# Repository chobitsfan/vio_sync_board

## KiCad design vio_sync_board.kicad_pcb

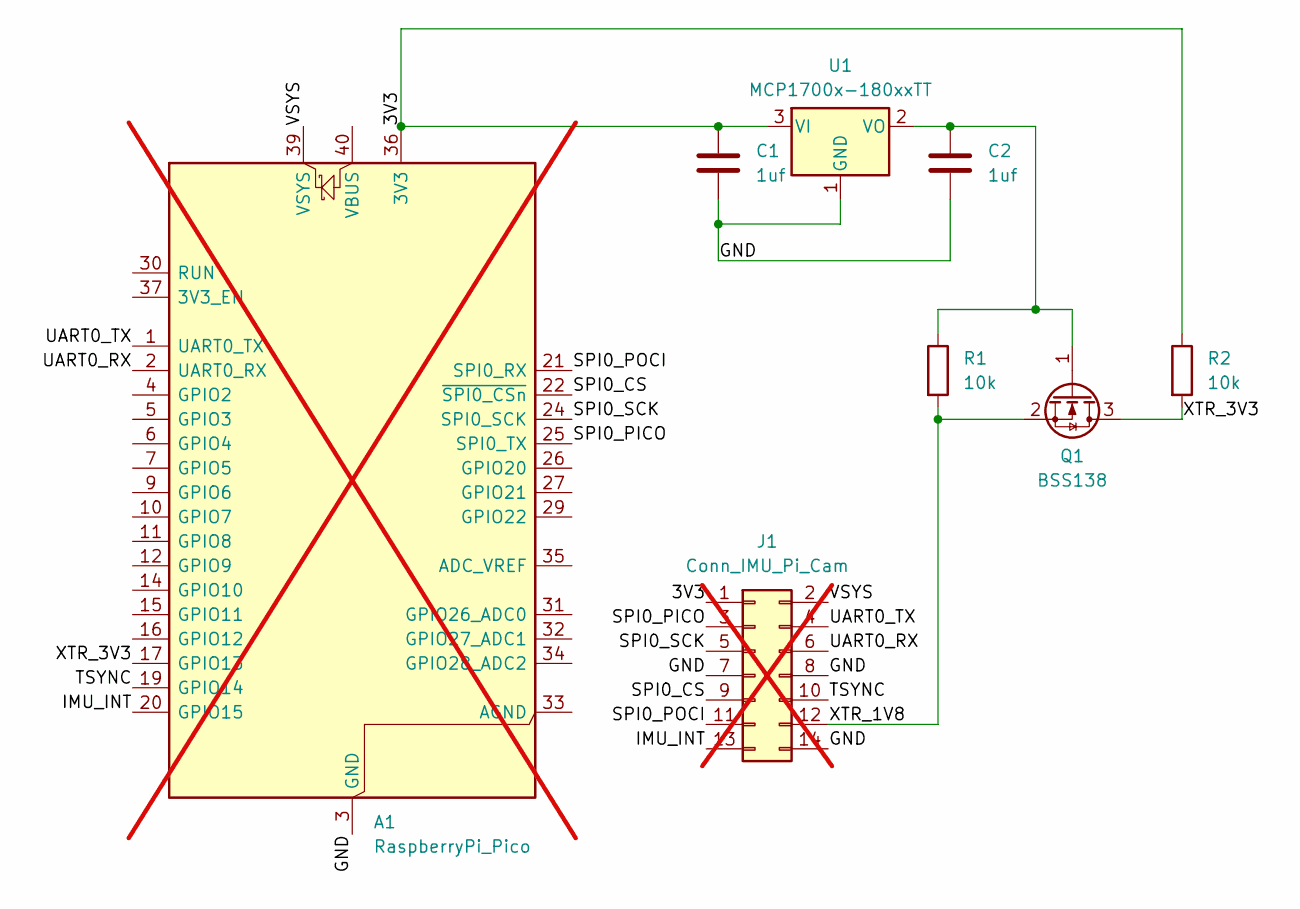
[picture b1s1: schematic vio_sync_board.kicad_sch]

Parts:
A1: RaspberryPi_Pico; RaspberryPi_Pico_Common_THT; not fitted
C1, C2: 1uf; C_0805_2012Metric
J1: Conn_IMU_Pi_Cam; PinHeader_2x07_P2.54mm_Vertical; not fitted
Q1: BSS138; SOT-23
R1, R2: 10k; R_0805_2012Metric
U1: MCP1700x-180xxTT; SOT-23

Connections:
/3V3: A1.36 (3V3), C1.1, J1.1, R2.1, U1.3 (VI)
/GND: A1.3 (GND), A1.8 (GND), A1.13 (GND), A1.18 (GND), A1.23 (GND), A1.28 (GND), A1.38 (GND), C1.2, C2.2, J1.7, J1.8, J1.14, U1.1 (GND)
/IMU_INT: A1.20 (GPIO15), J1.13
/SPI0_CS: A1.22 (~SPI0_CSn), J1.9
/SPI0_PICO: A1.25 (SPI0_TX), J1.3
/SPI0_POCI: A1.21 (SPI0_RX), J1.11
/SPI0_SCK: A1.24 (SPI0_SCK), J1.5
/TSYNC: A1.19 (GPIO14), J1.10
/UART0_RX: A1.2 (UART0_RX), J1.6
/UART0_TX: A1.1 (UART0_TX), J1.4
/VSYS: A1.39 (VSYS), J1.2
/XTR_1V8: J1.12, Q1.2 (S), R1.2
/XTR_3V3: A1.17 (GPIO13), Q1.3 (D), R2.2
unnamed: C2.1, Q1.1 (G), R1.1, U1.2 (VO)

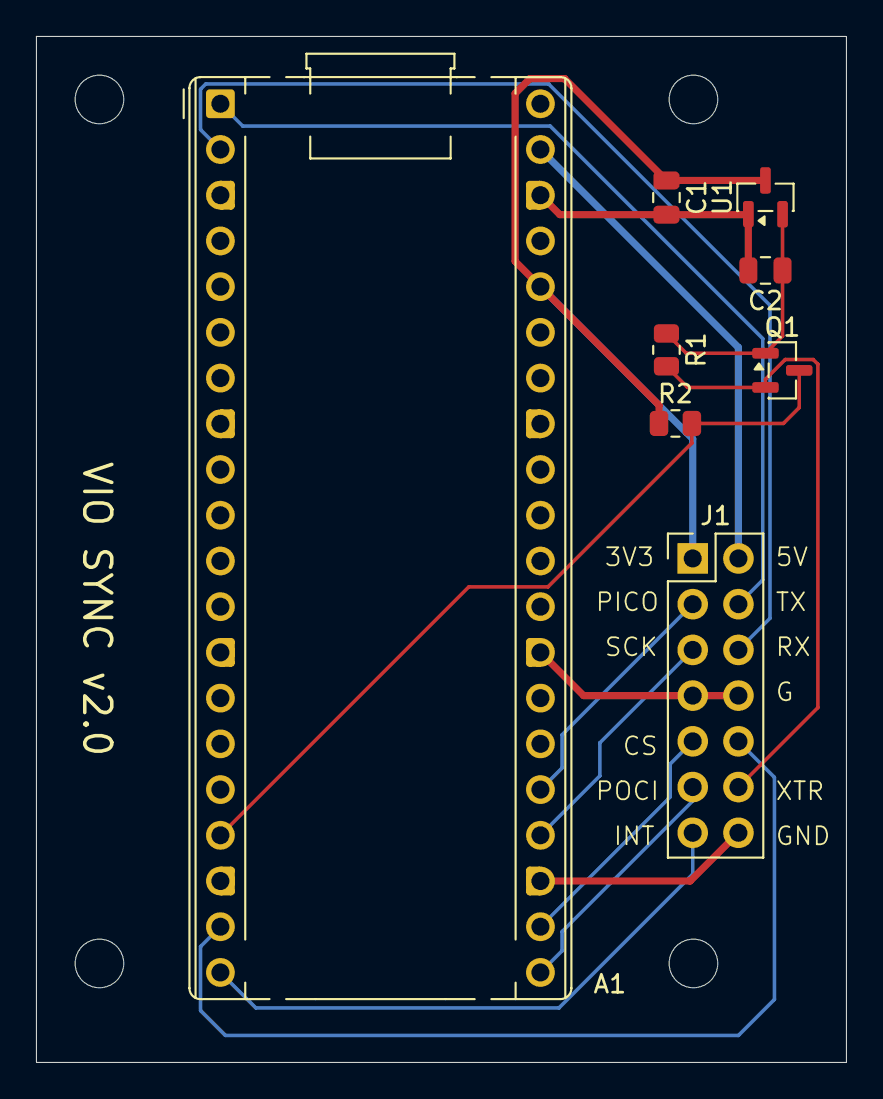
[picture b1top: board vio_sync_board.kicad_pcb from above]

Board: 2 copper layers, 45.0 x 57.0 mm, 8 parts (0 on the bottom side), 14 nets.

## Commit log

2026-01-14 layout
2026-01-15 fix traces, add text
2026-01-16 add logic level shifter symbol and footprint
2026-01-16 update 1.8v dc convert footprint
2026-02-11 add connector
2026-02-11 replace pololu dc converter and logic lv shifter
2026-02-11 resistor and capacitor footprint
2026-02-12 fix connector footprint
2026-02-12 start updating layout, not finished
2026-02-22 maybe we should split header to 3?
2026-02-24 refine pin header
2026-02-24 add mounting hole
2026-02-24 refine header and hole position
2026-02-25 track width
2026-02-25 DNP pico & header
